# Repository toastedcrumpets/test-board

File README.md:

# Inspirations

* Design rules from here https://github.com/reitermarkus/KiCad-DesignRules/tree/main
* Github Template to build pcb files for JLCPCB https://github.com/RickP/KiCad_JLC_template

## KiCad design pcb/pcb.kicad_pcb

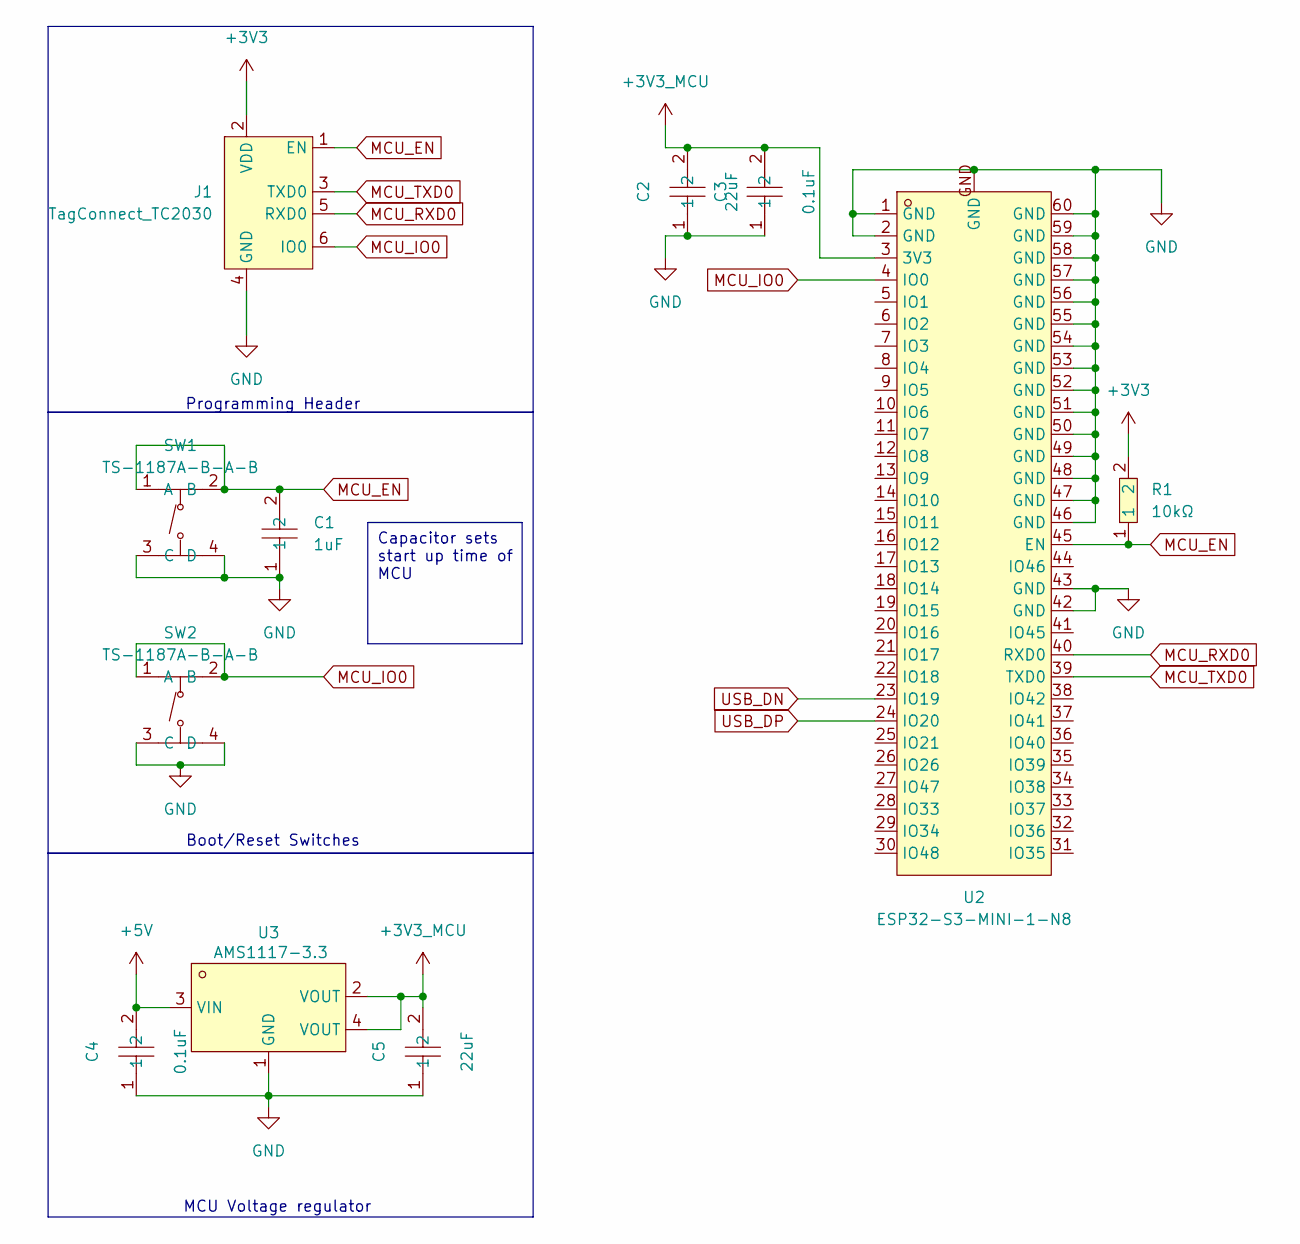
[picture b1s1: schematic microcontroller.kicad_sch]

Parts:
C1: 1uF; C0603; LCSC Part C15849
C2, C5: 22uF; C0603; LCSC Part C59461
C3, C4: 0.1uF; C0603; LCSC Part C14663
J1: TagConnect_TC2030; Tag-Connect_TC2030-IDC-FP_2x03_P1.27mm_Vertical
R1: 10kΩ; R0603; LCSC Part C25804
SW1, SW2: TS-1187A-B-A-B; SW-SMD_4P-L5.1-W5.1-P3.70-LS6.5-TL-2; LCSC Part C318884
U2: ESP32-S3-MINI-1-N8; BULETM-SMD_ESP32-S3-MINI-1-N8; LCSC Part C2913206
U3: AMS1117-3.3; SOT-223-3_L6.5-W3.4-P2.30-LS7.0-BR; LCSC Part C6186

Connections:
+3V3: J1.2 (VDD), R1.2
+3V3_MCU: C2.2, C3.2, C5.2, U2.3 (3V3), U3.2 (VOUT), U3.4 (VOUT)
+5V: C4.2, U3.3 (VIN)
GND: C1.1, C2.1, C3.1, C4.1, C5.1, J1.4 (GND), SW1.3 (C), SW1.4 (D), SW2.3 (C), SW2.4 (D), U2.1 (GND), U2.2 (GND), U2.42 (GND), U2.43 (GND), U2.46 (GND), U2.47 (GND), U2.48 (GND), U2.49 (GND), U2.50 (GND), U2.51 (GND), U2.52 (GND), U2.53 (GND), U2.54 (GND), U2.55 (GND), U2.56 (GND), U2.57 (GND), U2.58 (GND), U2.59 (GND), U2.60 (GND), U2.GND, U3.1 (GND); also elsewhere on the board
MCU_EN: C1.2, J1.1 (EN), R1.1, SW1.1 (A), SW1.2 (B), U2.45 (EN)
MCU_IO0: J1.6 (IO0), SW2.1 (A), SW2.2 (B), U2.4 (IO0)
MCU_RXD0: J1.5 (RXD0), U2.40 (RXD0)
MCU_TXD0: J1.3 (TXD0), U2.39 (TXD0)
USB_DN: U2.23 (IO19); also elsewhere on the board
USB_DP: U2.24 (IO20); also elsewhere on the board

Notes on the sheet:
Capacitor sets start up time of MCU
Programming Header
Boot/Reset Switches
MCU Voltage regulator

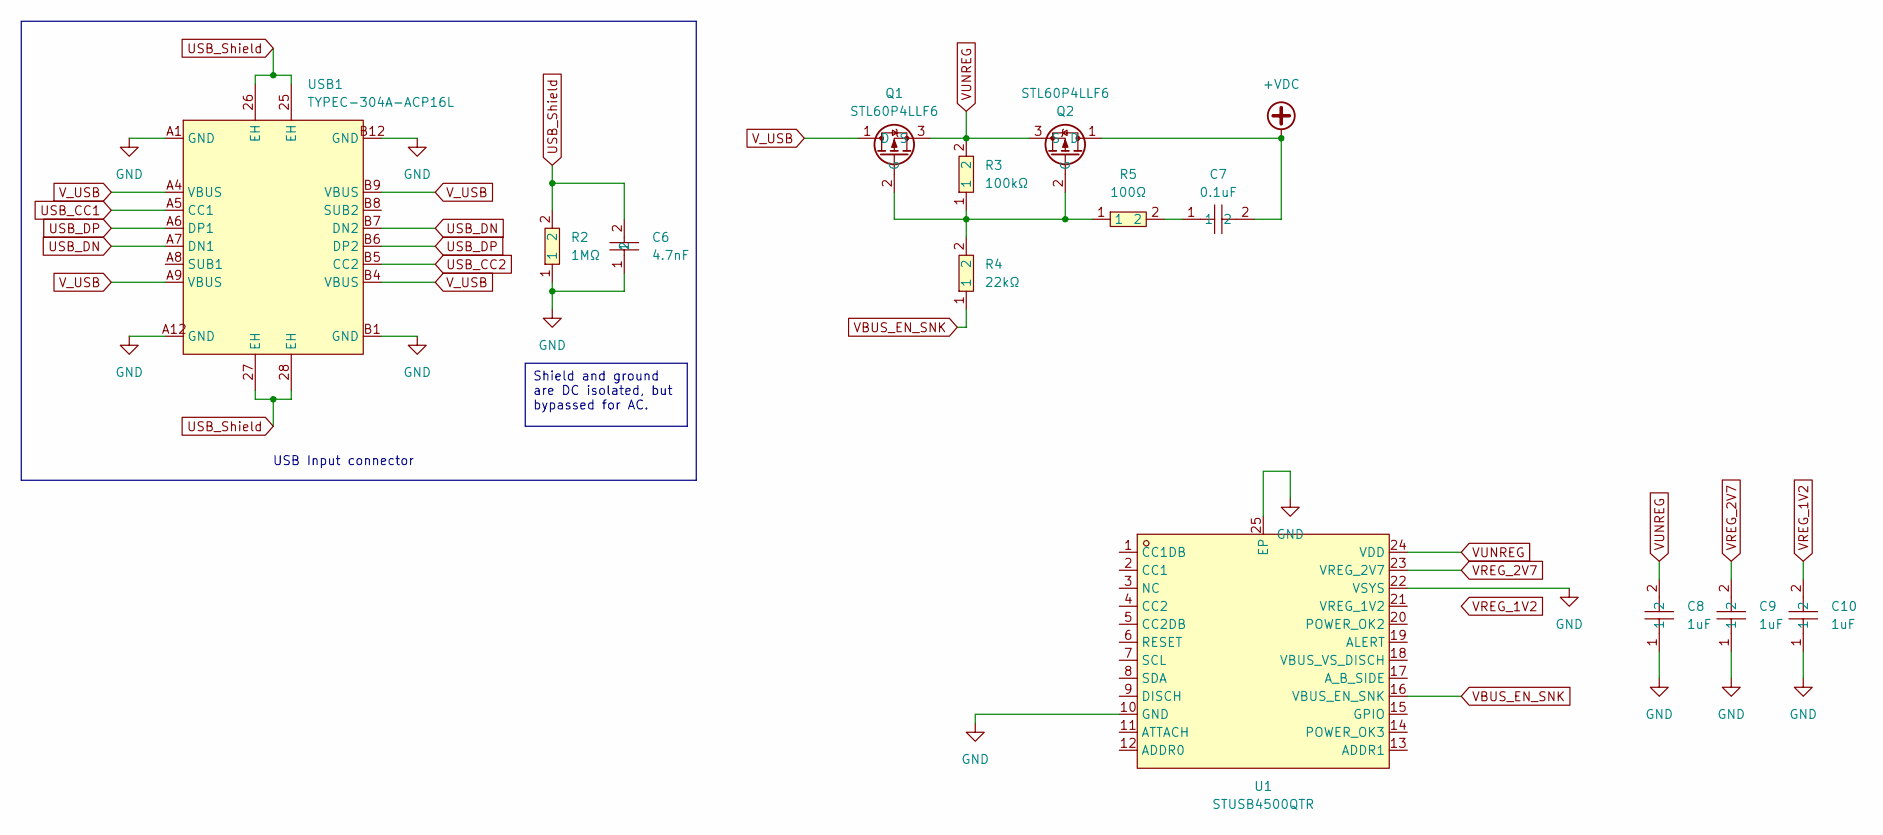
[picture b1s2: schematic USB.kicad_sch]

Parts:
C6: 4.7nF; C0603; LCSC Part C53987
C7: 0.1uF; C0603; LCSC Part C14663
C8, C9, C10: 1uF; C0603; LCSC Part C15849
Q1, Q2: STL60P4LLF6; POWERFLAT-8_L5.2-W6.0-P1.27-LS6.2-BL; LCSC Part C2688588
R2: 1MΩ; R0603; LCSC Part C22935
R3: 100kΩ; R0603; LCSC Part C25803
R4: 22kΩ; R0603; LCSC Part C31850
R5: 100Ω; R0603; LCSC Part C22775
U1: STUSB4500QTR; QFN-24_L4.0-W4.0-P0.50-BL-EP2.8; LCSC Part C2678061
USB1: TYPEC-304A-ACP16L; USB-C-SMD_XUNPU_TYPEC-304A-ACP16L; LCSC Part C2909609

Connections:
+VDC: C7.2, Q2.1 (D)
GND: C6.1, C8.1, C9.1, C10.1, R2.1, U1.10 (GND), U1.22 (VSYS), U1.25 (EP), USB1.A1 (GND), USB1.A12 (GND), USB1.B1 (GND), USB1.B12 (GND); also elsewhere on the board
unnamed: C7.1, R5.2
unnamed: Q1.2 (G), Q2.2 (G), R3.1, R4.2, R5.1
USB_CC1: USB1.A5 (CC1)
USB_CC2: USB1.B5 (CC2)
USB_DN: USB1.A7 (DN1), USB1.B7 (DN2); also elsewhere on the board
USB_DP: USB1.A6 (DP1), USB1.B6 (DP2); also elsewhere on the board
USB_Shield: C6.2, R2.2, USB1.25 (EH), USB1.26 (EH), USB1.27 (EH), USB1.28 (EH)
VBUS_EN_SNK: R4.1, U1.16 (VBUS_EN_SNK)
VREG_1V2: C10.2
VREG_2V7: C9.2, U1.23 (VREG_2V7)
VUNREG: C8.2, Q1.3 (S), Q2.3 (S), R3.2, U1.24 (VDD)
V_USB: Q1.1 (D), USB1.A4 (VBUS), USB1.A9 (VBUS), USB1.B4 (VBUS), USB1.B9 (VBUS)

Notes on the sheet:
Shield and ground are DC isolated, but bypassed for AC.
USB Input connector

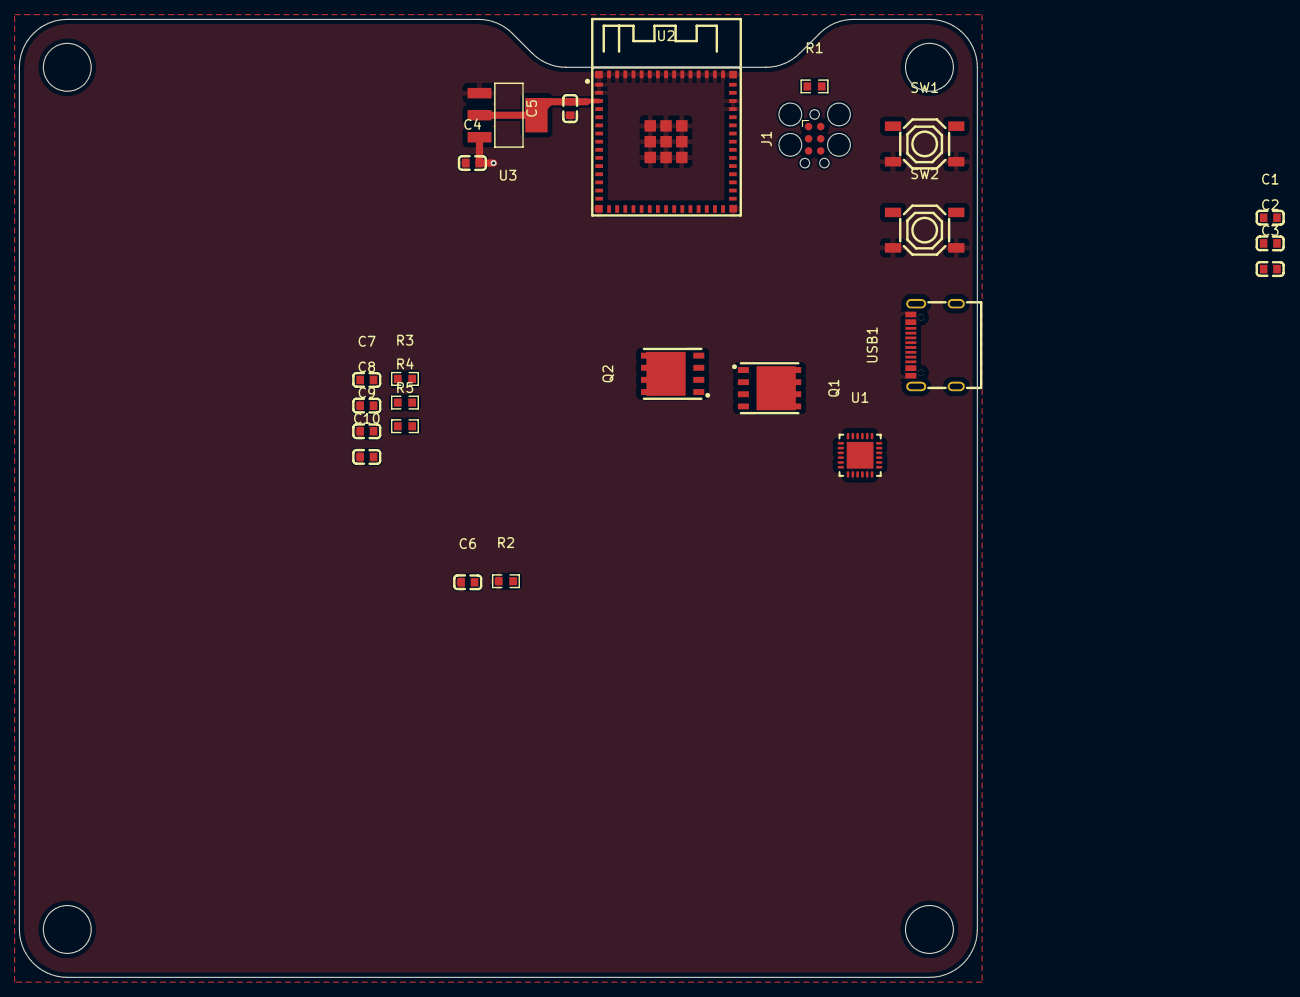
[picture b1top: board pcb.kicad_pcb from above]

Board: 4 copper layers, 100.0 x 100.0 mm, 24 parts (0 on the bottom side), 18 nets.

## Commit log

2024-10-18 Fix for the workflow file location
2024-10-18 Got LCSC part import working
2024-10-18 More playing with JLCPCB
2024-10-18 Fixed USB-C placement
2024-10-28 Much more work
2024-10-28 Starting on the SMPS
2024-10-29 Added note on ceramic caps
2025-01-25 Attempt at a firmware
2025-01-29 Got the idf compiling in a docker
